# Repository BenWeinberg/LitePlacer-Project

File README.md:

# LitePlacer-Project
 My Lightplacer build of January 2021

Build notes in no particular order:

The cable, 24 AWG shielded was selected for its size and flexibility.  They use about 1/4 the capacity of the cable chain, and are easy to work with.
The X and Y limit switches use one cable each, saving 2 cables in the chain.  The cable easily handles the current draw from the motors without getting warm.

The TinyG enclosure was found on a 3D print website and mounts easily to the frame of the Lightplacer.  This keeps the cables short and manageable.
https://www.thingiverse.com/thing:745369

I fabricated a pc board to hold 2 mosfets and 2 diodes for driving the vacuum and solenoid valve.  The mosfets I used were massively overspeced but I use them in other products and had them is stock.  There are many others in an SO8 package that would work fine.
This board is shared on OshPark.  https://oshpark.com/shared_projects/BAFElEDY

A second board was fabricated to add a switch for the Z limit switches to reverse them when switching between Liteplacer and OpenPNP.  Also shared on OshPark.  https://oshpark.com/shared_projects/8oBLMgzI

A 3rd board makes a clean interface in the TinyG controller for the led power leads.  Also shared on OshPark.  https://oshpark.com/shared_projects/RTm1xfcH

The table was selected based on another builders choice that looked like it would work well.  It turned out to be a good choice, being very rigid but light-weight, and definitely low-priced.  Care must be taken to not over-tighten the wood screws that hold down the LP frame.  The 4 corners where the legs attach are reinforced internally with solid wood, but the rest of the table is just cardboard inside.  I have included 2 photos of the hole removed by a hole saw to provide for the up-camera view.

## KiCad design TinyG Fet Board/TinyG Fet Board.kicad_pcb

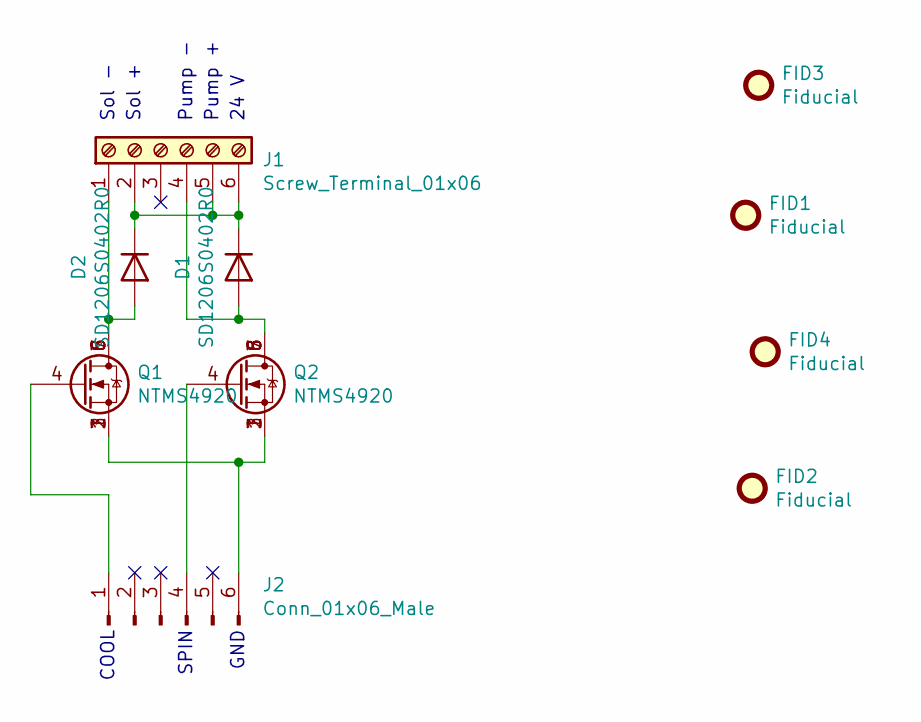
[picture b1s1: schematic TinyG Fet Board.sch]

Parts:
D1, D2: SD1206S0402R0; D_1206_3216Metric
FID1, FID2, FID3, FID4: Fiducial; Fiducial_1mm_Mask2mm
J1: Screw_Terminal_01x06; Wuerth 691243310006
J2: Conn_01x06_Male; 6_Pin_Header_.150
Q1, Q2: NTMS4920; SO-08

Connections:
unnamed: D1.1 (K), D2.1 (K), J1.2, J1.5, J1.6
unnamed: D1.2 (A), J1.4, Q2.5 (D), Q2.6 (D), Q2.7 (D), Q2.8 (D)
unnamed: D2.2 (A), J1.1, Q1.5 (D), Q1.6 (D), Q1.7 (D), Q1.8 (D)
unnamed: J2.1, Q1.4 (G)
unnamed: J2.4, Q2.4 (G)
unnamed: J2.6, Q1.1 (S), Q1.2 (S), Q1.3 (S), Q2.1 (S), Q2.2 (S), Q2.3 (S)

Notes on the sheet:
Sol -
Sol +
Pump -
Pump +
24 V
GND
COOL
SPIN

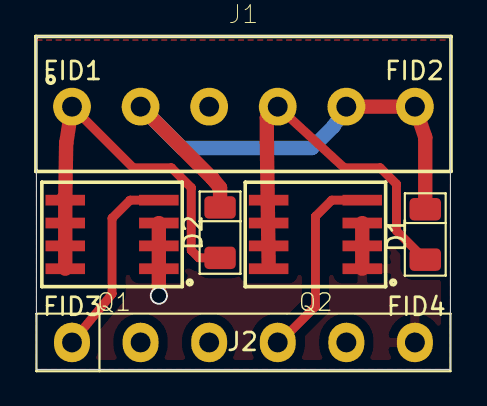
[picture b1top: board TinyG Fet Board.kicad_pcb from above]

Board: 2 copper layers, 23.0 x 18.5 mm, 10 parts (0 on the bottom side), 6 nets.

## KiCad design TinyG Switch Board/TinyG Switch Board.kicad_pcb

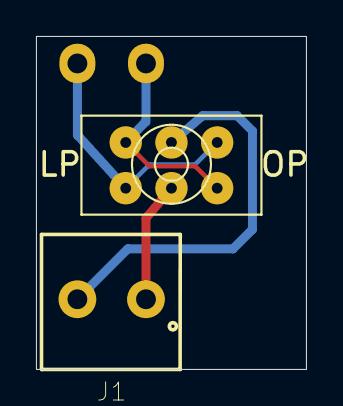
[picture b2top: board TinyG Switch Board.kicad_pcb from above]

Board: 2 copper layers, 15.0 x 18.5 mm, 3 parts (0 on the bottom side), 4 nets.

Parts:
J1: Screw_Terminal_01x02; ScrewTerminal_.150_x2
J2: Conn_01x02_Male; 2_Pin_Header_.150
SW1: SW_DPDT; NKK G22 SPST Switch

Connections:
unnamed: J1.1, SW1.5
unnamed: J1.2, SW1.2
unnamed: J2.1, SW1.1, SW1.6
unnamed: J2.2, SW1.3, SW1.4

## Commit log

2021-02-03 Lightplacer build of January 2021
    Here are the details of my Lightplacer build.
